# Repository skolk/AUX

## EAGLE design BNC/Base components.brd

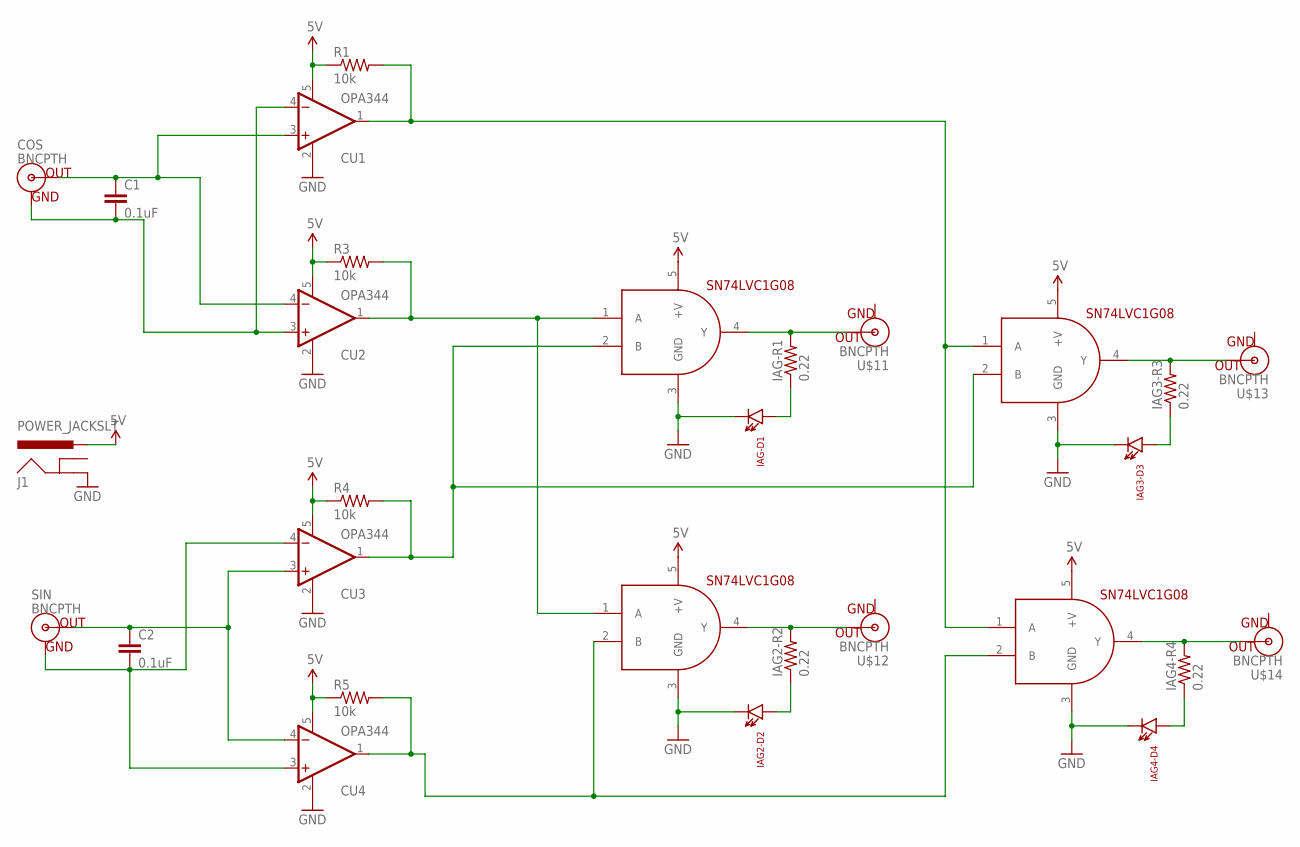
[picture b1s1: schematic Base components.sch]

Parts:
C1, C2: 0.1uF; 0603-CAP
COS: BNCPTH; BNC
CU1, CU2, CU3, CU4: OPA344; SOT23-5
IAG1, IAG2, IAG3, IAG4: SN74LVC1G08; SOT23-5
IAG2-D2, IAG3-D3, IAG4-D4: LTE-302
IAG2-R2, IAG3-R3, IAG4-R4: 0.22; 0805
IAG-D1: LTE-302
IAG-R1: 0.22; 0805
J1: POWER_JACKSLT; POWER_JACK_SLOT
R1, R3, R4, R5: 10k; AXIAL-0.3
SIN: BNCPTH; BNC
U$11, U$12, U$13, U$14: BNCPTH; BNC

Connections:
5V: CU1.5 (V+), CU2.5 (V+), CU3.5 (V+), CU4.5 (V+), IAG1.5 (+V), IAG2.5 (+V), IAG3.5 (+V), IAG4.5 (+V), J1.PWR, R1.P$1 (1), R3.P$1 (1), R4.P$1 (1), R5.P$1 (1)
GND: CU1.2 (V-), CU2.2 (V-), CU3.2 (V-), CU4.2 (V-), IAG1.3 (GND), IAG2.3 (GND), IAG2-D2.C, IAG3.3 (GND), IAG3-D3.C, IAG4.3 (GND), IAG4-D4.C, IAG-D1.C, J1.GND@2 (GND)
unnamed: CU1.1 (OUT), IAG3.1 (A), IAG4.1 (A), R1.P$2 (2)
unnamed: IAG4.4 (Y), IAG4-R4.2, U$14.S (OUT)
unnamed: IAG4-D4.A, IAG4-R4.1
unnamed: CU2.1 (OUT), IAG1.1 (A), IAG2.1 (A), R3.P$2 (2)
unnamed: CU3.1 (OUT), IAG1.2 (B), IAG3.2 (B), R4.P$2 (2)
unnamed: CU4.1 (OUT), IAG2.2 (B), IAG4.2 (B), R5.P$2 (2)
unnamed: C1.2, COS.GND, CU1.4 (-IN), CU2.3 (+IN)
unnamed: C1.1, COS.S (OUT), CU1.3 (+IN), CU2.4 (-IN)
unnamed: C2.1, CU3.3 (+IN), CU4.4 (-IN), SIN.S (OUT)
unnamed: C2.2, CU3.4 (-IN), CU4.3 (+IN), SIN.GND
unnamed: IAG3.4 (Y), IAG3-R3.2, U$13.S (OUT)
unnamed: IAG3-D3.A, IAG3-R3.1
unnamed: IAG2.4 (Y), IAG2-R2.2, U$12.S (OUT)
unnamed: IAG2-D2.A, IAG2-R2.1
unnamed: IAG1.4 (Y), IAG-R1.2, U$11.S (OUT)
unnamed: IAG-D1.A, IAG-R1.1

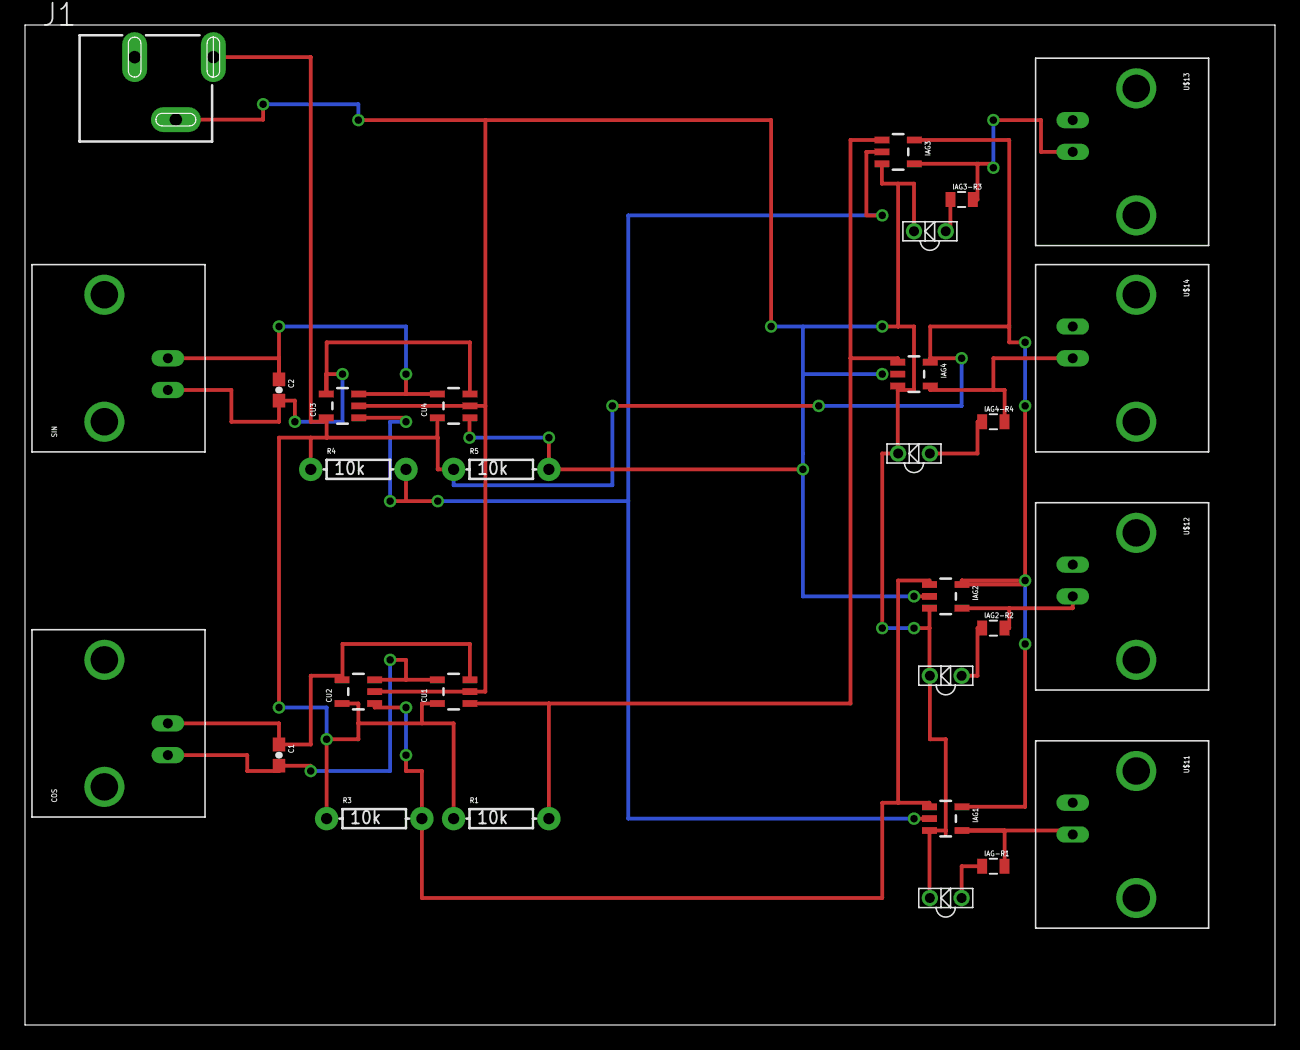
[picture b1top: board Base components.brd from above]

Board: 2 copper layers, 100.0 x 80.0 mm, 29 parts (0 on the bottom side), 18 nets.

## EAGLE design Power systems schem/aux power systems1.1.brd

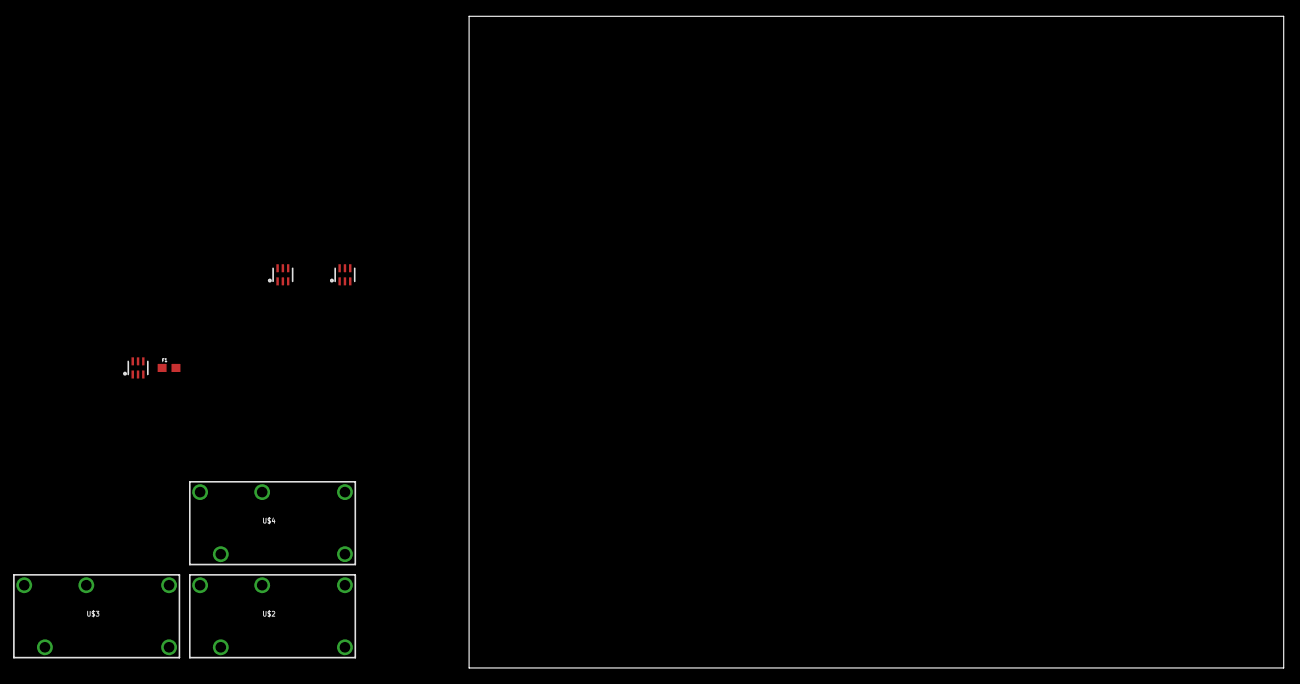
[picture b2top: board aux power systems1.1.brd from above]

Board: 2 copper layers, 100.0 x 80.0 mm, 7 parts (0 on the bottom side), 8 nets, no tracks yet.

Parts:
F1: PTC0603; 0603
U$2, U$3, U$4: RELAYPTH; RELAY-G5Q
U$9, U$13, U$15: BC847PN; SOT363

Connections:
5V: U$9.3, U$13.3, U$15.3
AGND: U$2.5, U$4.1
B$2: U$2.3, U$3.3, U$4.3
unnamed: U$3.5, U$9.4
unnamed: U$4.5, U$13.4
unnamed: U$2.1, U$15.4
unnamed: F1.1, F1.2
unnamed: U$3.2, U$4.2

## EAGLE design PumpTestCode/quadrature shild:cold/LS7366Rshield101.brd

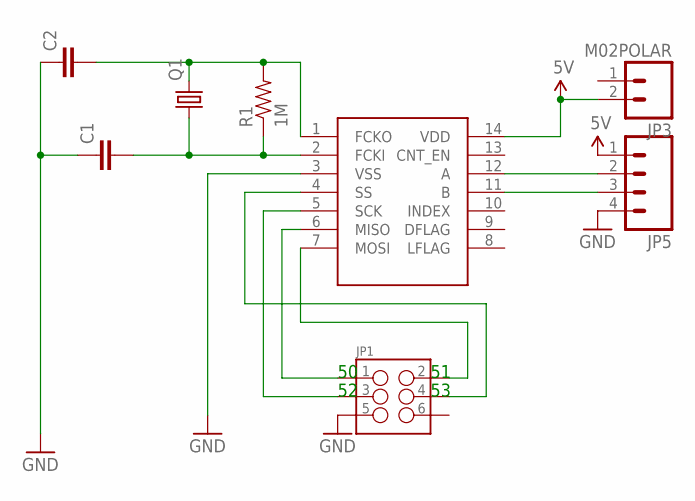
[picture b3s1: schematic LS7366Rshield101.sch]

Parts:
C1, C2: 0.1UF-50V-20%(PTH)KIT-EZ; CAP-PTH-SMALL-KIT
JP1: M03X2POGO_PINS; 2X3_POGO
JP3: M02POLAR; MOLEX-1X2
JP5: M04POLAR; MOLEX-1X4
LS7366R: LS7366R; SO014
Q1: CRYSTALHC49S; HC49/S
R1: 1M; AXIAL-0.3

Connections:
5V: JP3.2, JP5.1, LS7366R.14 (VDD)
GND: C1.1, C2.1, JP1.P$5 (5), JP5.4, LS7366R.3 (VSS)
unnamed: C1.2, LS7366R.2 (FCKI), Q1.1, R1.P$1 (1)
unnamed: C2.2, LS7366R.1 (FCKO), Q1.2, R1.P$2 (2)
unnamed: JP1.P$1 (1), LS7366R.6 (MISO)
unnamed: JP1.P$4 (4), LS7366R.4 (SS)
unnamed: JP1.P$2 (2), LS7366R.7 (MOSI)
unnamed: JP1.P$3 (3), LS7366R.5 (SCK)
unnamed: JP5.2, LS7366R.12 (A)
unnamed: JP5.3, LS7366R.11 (B)

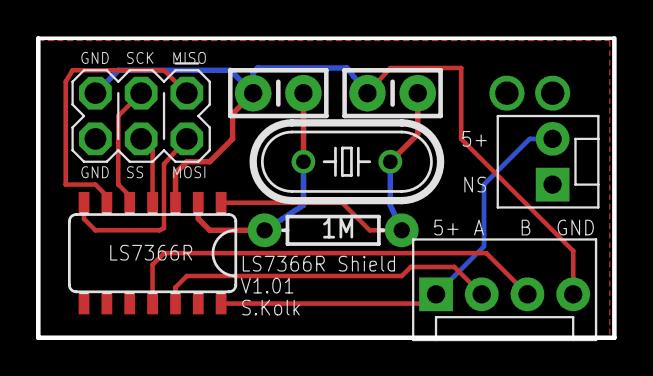
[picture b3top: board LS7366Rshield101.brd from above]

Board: 2 copper layers, 32.0 x 16.6 mm, 8 parts (0 on the bottom side), 10 nets.

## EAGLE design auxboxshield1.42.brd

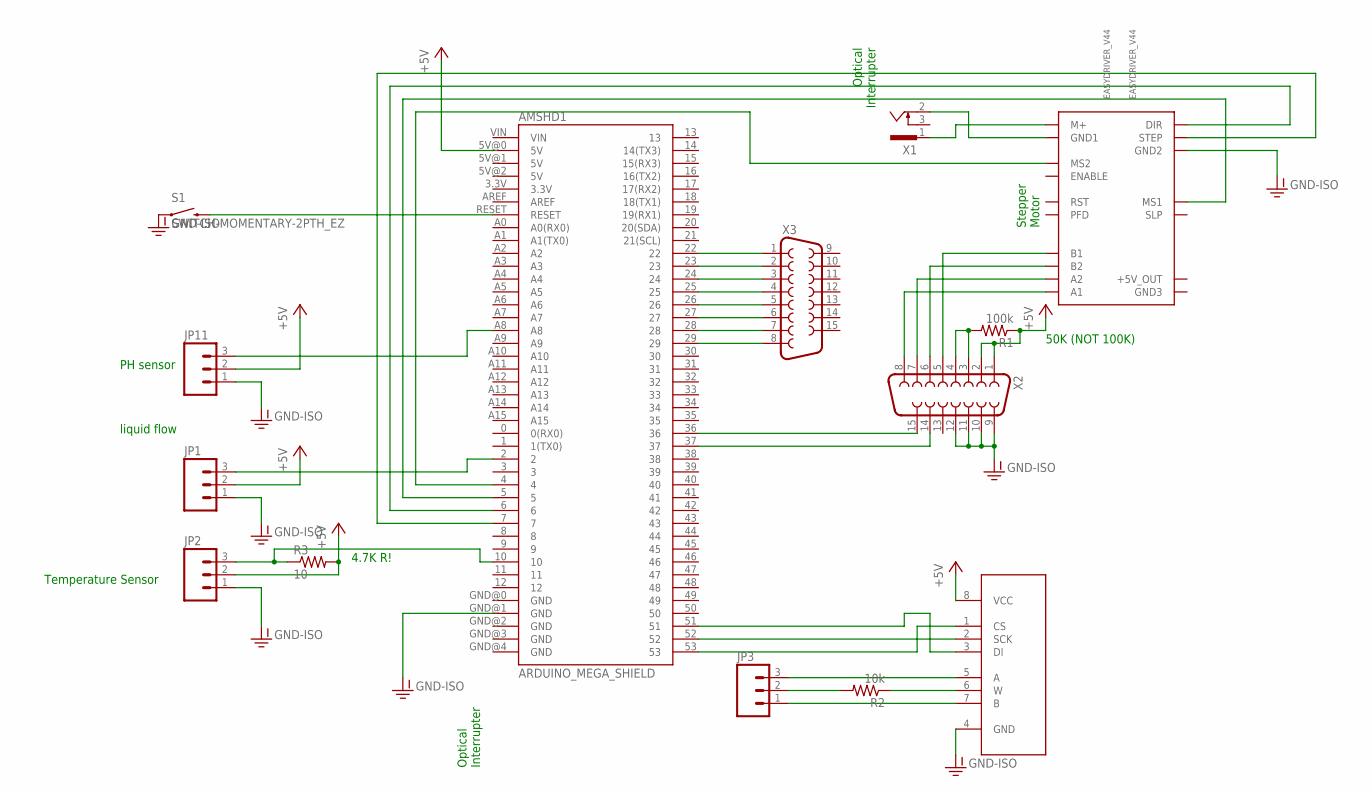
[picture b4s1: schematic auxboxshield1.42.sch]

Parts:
AMSHD1: ARDUINO_MEGA_SHIELD
EASYDRIVER_V44: EASYDRIVER_V44
JP1, JP2, JP3, JP11: M03POLAR; MOLEX-1X3
R1: 100k; AXIAL-0.3
R2: 10k; AXIAL-0.3
R3: 10; AXIAL-0.3
S1: SWITCH-MOMENTARY-2PTH_EZ; TACTILE-PTH-EZ
U1: MCP41XXX; SO08
X1: SCD-014A; SCD-014-A
X2, X3: F15HP

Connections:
+5V: AMSHD1.5V@0 (5V), JP1.2, JP2.2, JP11.2, R1.P$1 (1), R3.P$2 (2), U1.8 (VCC), X2.1, X2.2
GND-ISO: AMSHD1.GND@1 (GND), EASYDRIVER_V44.GND2, JP1.1, JP2.1, JP11.1, S1.1, U1.4 (GND), X2.9, X2.10, X2.11, X2.12
unnamed: EASYDRIVER_V44.M+, X1.1
unnamed: EASYDRIVER_V44.A1, X2.8
unnamed: EASYDRIVER_V44.A2, X2.7
unnamed: R1.P$2 (2), X2.3, X2.4
unnamed: AMSHD1.22, X3.1
unnamed: EASYDRIVER_V44.GND1, X1.2
unnamed: EASYDRIVER_V44.B2, X2.6
unnamed: AMSHD1.23, X3.2
unnamed: AMSHD1.RESET, S1.3 (2)
unnamed: AMSHD1.24, X3.3
unnamed: EASYDRIVER_V44.B1, X2.5
unnamed: AMSHD1.53, U1.1 (CS)
unnamed: AMSHD1.5, EASYDRIVER_V44.MS1
unnamed: AMSHD1.25, X3.4
unnamed: AMSHD1.A8, JP11.3
unnamed: AMSHD1.4, EASYDRIVER_V44.MS2
unnamed: AMSHD1.52, U1.2 (SCK)
unnamed: AMSHD1.26, X3.5
unnamed: AMSHD1.27, X3.6
unnamed: AMSHD1.51, U1.3 (DI)
unnamed: JP3.3, U1.5 (A)
unnamed: AMSHD1.28, X3.7
unnamed: AMSHD1.29, X3.8
unnamed: R2.P$1 (1), U1.6 (W)
unnamed: JP3.2, R2.P$2 (2)
unnamed: AMSHD1.10, JP2.3, R3.P$1 (1)
unnamed: AMSHD1.2, JP1.3
unnamed: AMSHD1.6, EASYDRIVER_V44.DIR
unnamed: AMSHD1.7, EASYDRIVER_V44.STEP
unnamed: JP3.1, U1.7 (B)
unnamed: AMSHD1.36, X2.15
unnamed: AMSHD1.37, X2.14

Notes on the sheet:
Stepper Motor
Optical Interrupter
Temperature Sensor
liquid flow
PH sensor
50K (NOT 100K)
4.7K R!

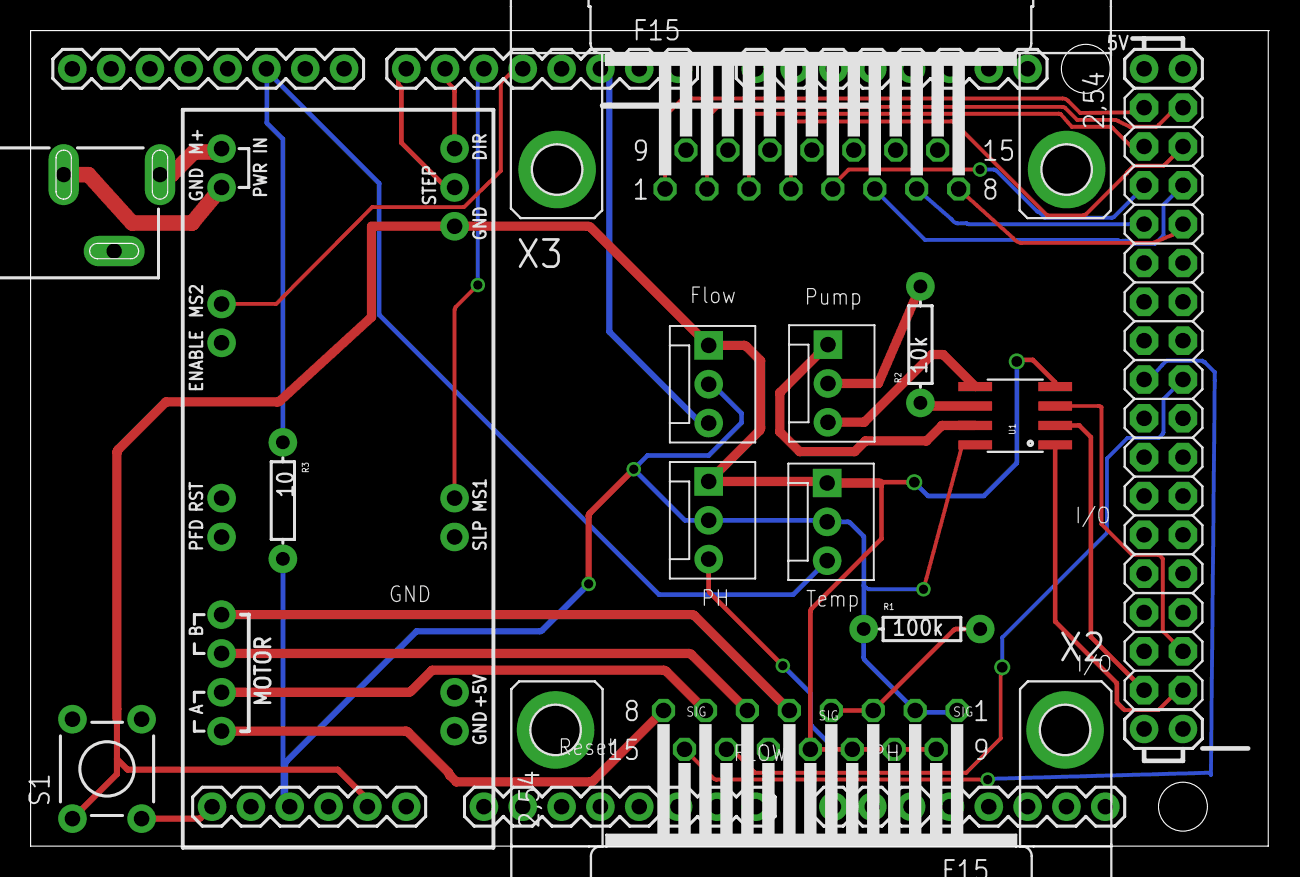
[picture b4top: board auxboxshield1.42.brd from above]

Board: 2 copper layers, 81.0 x 53.3 mm, 15 parts (0 on the bottom side), 34 nets.

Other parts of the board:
DRILEGEND: DRILEGEND

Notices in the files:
parts and their libraries:
SparkFun-AnalogIC: Licensing:Creative Commons ShareAlike 4.0 International - https://creativecommons.org/licenses/by-sa/4.0
